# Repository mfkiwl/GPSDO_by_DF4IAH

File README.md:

# GPSDO_by_DF4IAH
GNSS or DCF77 disciplined OCXO based on hardware by DL4ZAO and DL7UKM.

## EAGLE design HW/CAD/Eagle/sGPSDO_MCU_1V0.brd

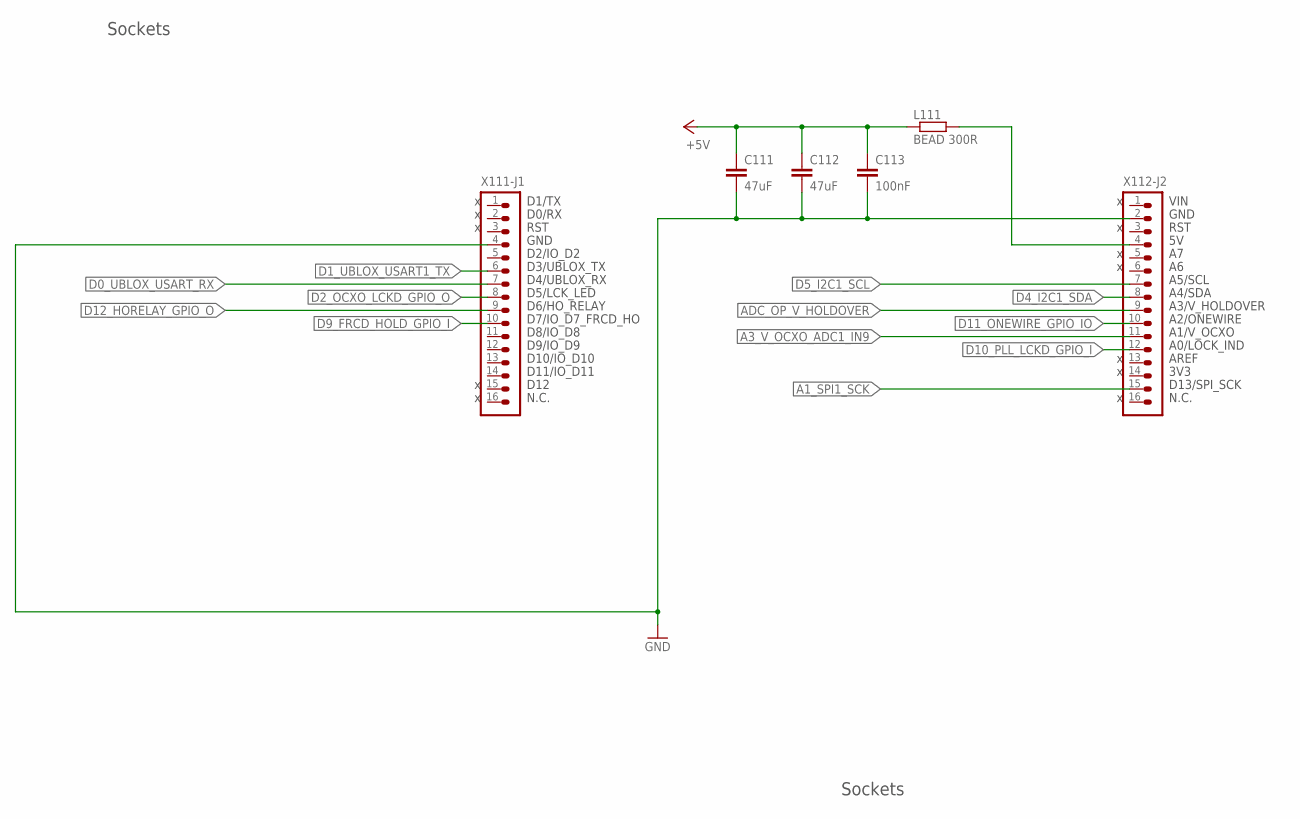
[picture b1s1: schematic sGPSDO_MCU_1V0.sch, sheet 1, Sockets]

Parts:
C111, C112: 47uF; C0805
C113: 100nF; C0805
L111: BEAD 300R; R1206
X111-J1, X112-J2: HEADER-1X16; 1X16

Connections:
+5V: C111.1, C112.1, C113.1, L111.1; also elsewhere on the board
A1_SPI1_SCK: X112-J2.15; also elsewhere on the board
A3_V_OCXO_ADC1_IN9: X112-J2.11; also elsewhere on the board
ADC_OP_V_HOLDOVER: X112-J2.9; also elsewhere on the board
D0_UBLOX_USART_RX: X111-J1.7; also elsewhere on the board
D1_UBLOX_USART1_TX: X111-J1.6; also elsewhere on the board
D2_OCXO_LCKD_GPIO_O: X111-J1.8; also elsewhere on the board
D4_I2C1_SDA: X112-J2.8; also elsewhere on the board
D5_I2C1_SCL: X112-J2.7; also elsewhere on the board
D9_FRCD_HOLD_GPIO_I: X111-J1.10; also elsewhere on the board
D10_PLL_LCKD_GPIO_I: X112-J2.12; also elsewhere on the board
D11_ONEWIRE_GPIO_IO: X112-J2.10; also elsewhere on the board
D12_HORELAY_GPIO_O: X111-J1.9; also elsewhere on the board
GND: C111.2, C112.2, C113.2, X111-J1.4, X112-J2.2; also elsewhere on the board
N112: L111.2, X112-J2.4

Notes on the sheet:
Sockets
A0/LOCK_IND
AREF
3V3
D13/SPI_SCK
N.C.
A1/V_OCXO
A2/ONEWIRE
A3/V_HOLDOVER
A4/SDA
A5/SCL
RST
GND
VIN
D12
D11/IO_D11
D10/IO_D10
D9/IO_D9
D8/IO_D8
D7/IO_D7_FRCD_HO
D6/HO_RELAY
D5/LCK_LED
D4/UBLOX_RX
D3/UBLOX_TX
D2/IO_D2
D0/RX
D1/TX

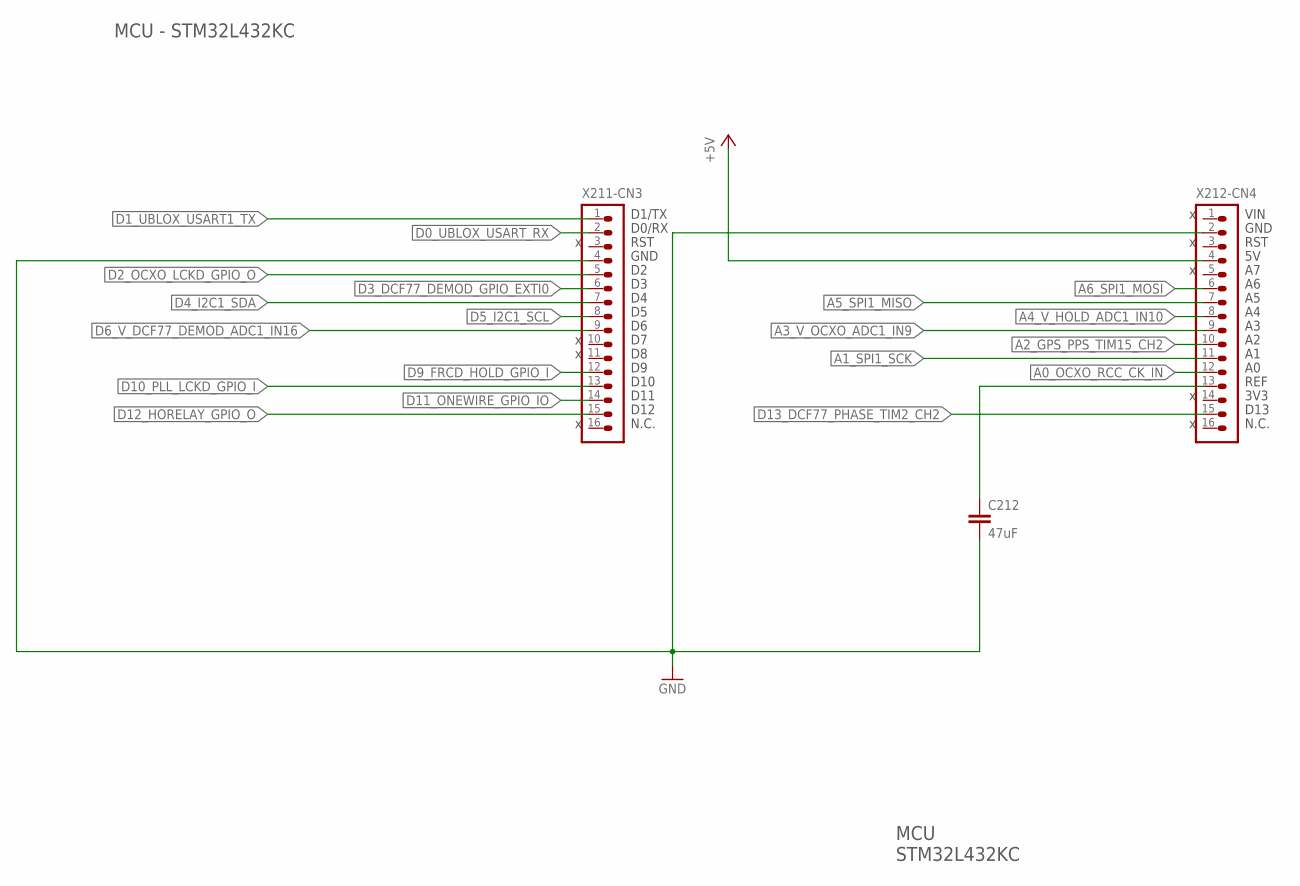
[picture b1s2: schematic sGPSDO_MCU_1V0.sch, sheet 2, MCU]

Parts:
C212: 47uF; C0805
X211-CN3, X212-CN4: HEADER-1X16; 1X16

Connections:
+5V: X212-CN4.4; also elsewhere on the board
A0_OCXO_RCC_CK_IN: X212-CN4.12; also elsewhere on the board
A1_SPI1_SCK: X212-CN4.11; also elsewhere on the board
A2_GPS_PPS_TIM15_CH2: X212-CN4.10; also elsewhere on the board
A3_V_OCXO_ADC1_IN9: X212-CN4.9; also elsewhere on the board
A4_V_HOLD_ADC1_IN10: X212-CN4.8; also elsewhere on the board
A5_SPI1_MISO: X212-CN4.7; also elsewhere on the board
A6_SPI1_MOSI: X212-CN4.6; also elsewhere on the board
D0_UBLOX_USART_RX: X211-CN3.2; also elsewhere on the board
D1_UBLOX_USART1_TX: X211-CN3.1; also elsewhere on the board
D2_OCXO_LCKD_GPIO_O: X211-CN3.5; also elsewhere on the board
D3_DCF77_DEMOD_GPIO_EXTI0: X211-CN3.6; also elsewhere on the board
D4_I2C1_SDA: X211-CN3.7; also elsewhere on the board
D5_I2C1_SCL: X211-CN3.8; also elsewhere on the board
D6_V_DCF77_DEMOD_ADC1_IN16: X211-CN3.9; also elsewhere on the board
D9_FRCD_HOLD_GPIO_I: X211-CN3.12; also elsewhere on the board
D10_PLL_LCKD_GPIO_I: X211-CN3.13; also elsewhere on the board
D11_ONEWIRE_GPIO_IO: X211-CN3.14; also elsewhere on the board
D12_HORELAY_GPIO_O: X211-CN3.15; also elsewhere on the board
D13_DCF77_PHASE_TIM2_CH2: X212-CN4.15; also elsewhere on the board
GND: C212.2, X211-CN3.4, X212-CN4.2; also elsewhere on the board
VREF: C212.1, X212-CN4.13

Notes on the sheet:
MCU - STM32L432KC
MCU STM32L432KC
REF
3V3
D13
N.C.
RST
GND
VIN
D12
D11
D10
D0/RX
D1/TX

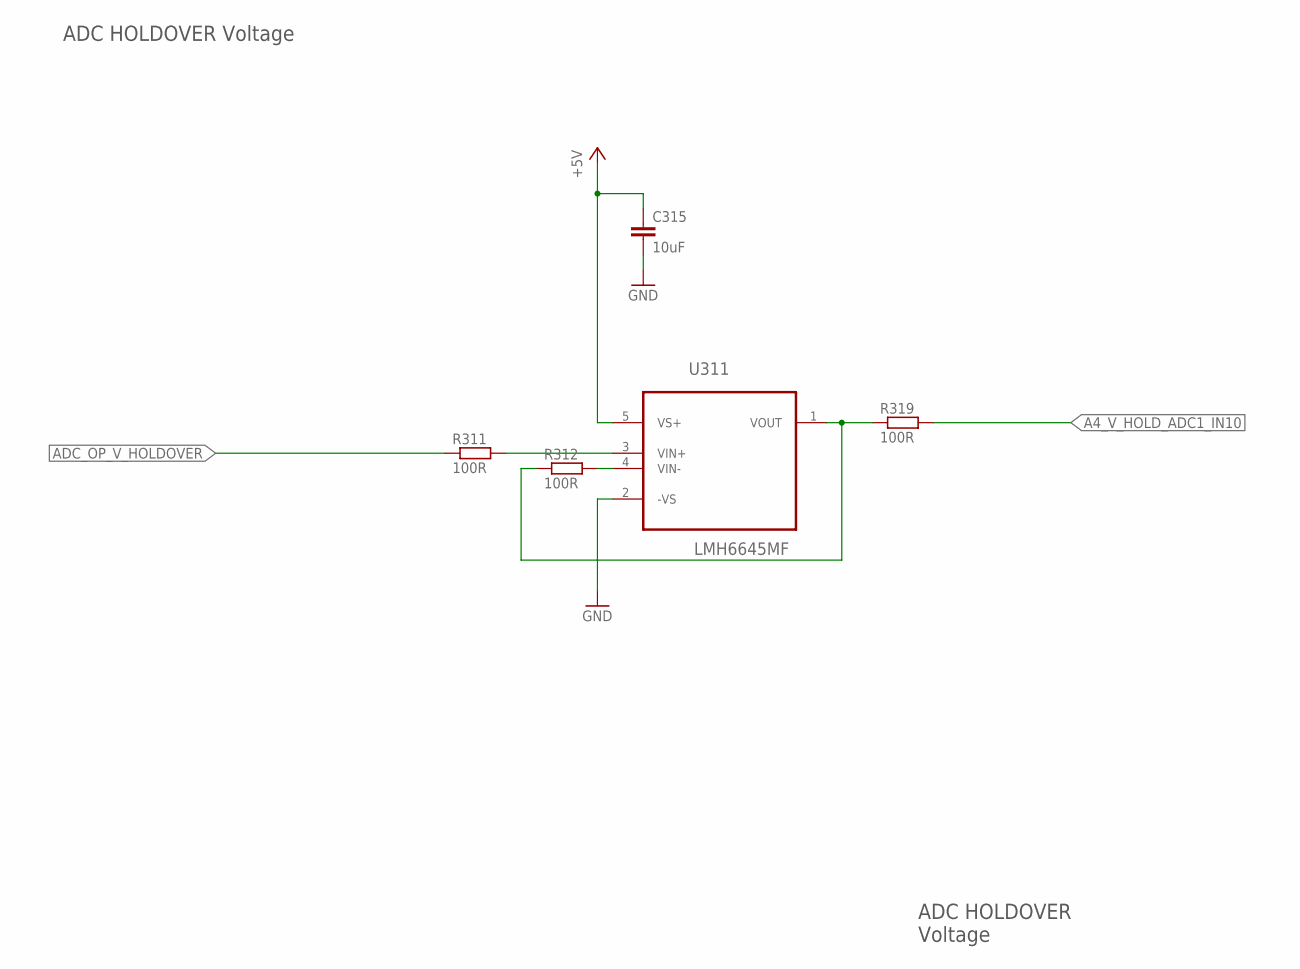
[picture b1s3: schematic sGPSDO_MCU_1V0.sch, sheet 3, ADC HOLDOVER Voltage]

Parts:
C315: 10uF; C0805
R311, R312, R319: 100R; R0805
U311: LMH6645MF; SOT-23-5

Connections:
+5V: C315.1, U311.5 (VS+); also elsewhere on the board
A4_V_HOLD_ADC1_IN10: R319.2; also elsewhere on the board
ADC_OP_V_HOLDOVER: R311.1; also elsewhere on the board
GND: C315.2, U311.2 (-VS); also elsewhere on the board
N311: R311.2, U311.3 (VIN+)
N312: R312.2, U311.4 (VIN-)
N319: R312.1, R319.1, U311.1 (VOUT)

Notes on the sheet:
ADC HOLDOVER Voltage
ADC HOLDOVER Voltage

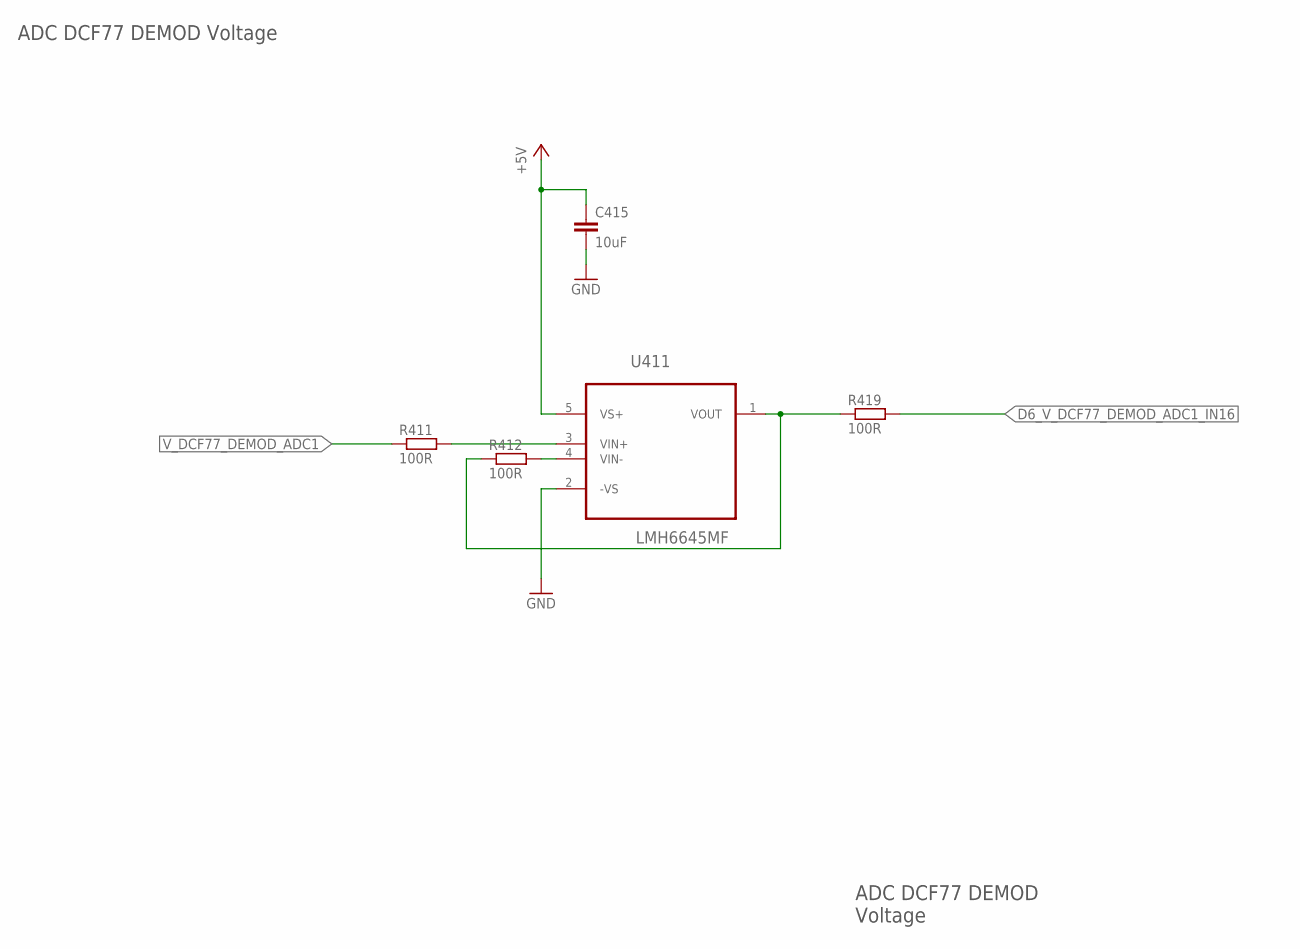
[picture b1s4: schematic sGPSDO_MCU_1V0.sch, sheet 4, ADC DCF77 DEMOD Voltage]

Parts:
C415: 10uF; C0805
R411, R412, R419: 100R; R0805
U411: LMH6645MF; SOT-23-5

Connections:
+5V: C415.1, U411.5 (VS+); also elsewhere on the board
D6_V_DCF77_DEMOD_ADC1_IN16: R419.2; also elsewhere on the board
GND: C415.2, U411.2 (-VS); also elsewhere on the board
N411: R411.2, U411.3 (VIN+)
N412: R412.2, U411.4 (VIN-)
N419: R412.1, R419.1, U411.1 (VOUT)
V_DCF77_DEMOD_ADC1: R411.1; also elsewhere on the board

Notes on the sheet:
ADC DCF77 DEMOD Voltage
ADC DCF77 DEMOD Voltage

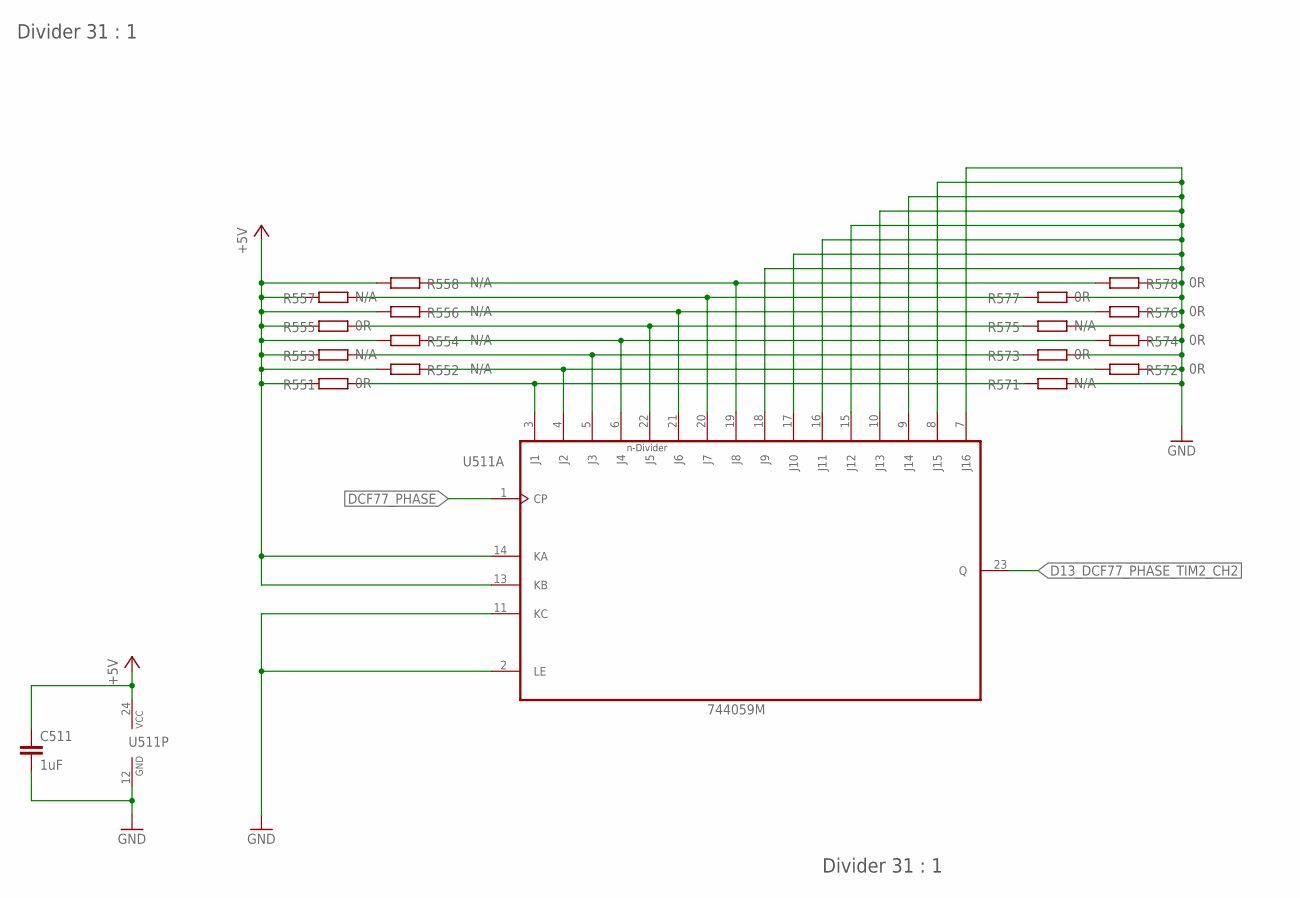
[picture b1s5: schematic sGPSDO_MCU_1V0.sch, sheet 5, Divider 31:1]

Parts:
C511: 1uF; C0805
R551, R555, R572, R573, R574, R576, R577, R578: 0R; R0402
R552, R553, R554, R556, R557, R558, R571, R575: N/A; R0402
U511: 744059M; SO24

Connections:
+5V: C511.1, R551.1, R552.1, R553.1, R554.1, R555.1, R556.1, R557.1, R558.1, U511.13 (KB), U511.14 (KA), U511.24 (VCC); also elsewhere on the board
D13_DCF77_PHASE_TIM2_CH2: U511.23 (Q); also elsewhere on the board
DCF77_PHASE: U511.1 (CP); also elsewhere on the board
GND: C511.2, R571.2, R572.2, R573.2, R574.2, R575.2, R576.2, R577.2, R578.2, U511.2 (LE), U511.7 (J16), U511.8 (J15), U511.9 (J14), U511.10 (J13), U511.11 (KC), U511.12 (GND), U511.15 (J12), U511.16 (J11), U511.17 (J10), U511.18 (J9); also elsewhere on the board
N551: R551.2, R571.1, U511.3 (J1)
N552: R552.2, R572.1, U511.4 (J2)
N553: R553.2, R573.1, U511.5 (J3)
N554: R554.2, R574.1, U511.6 (J4)
N555: R555.2, R575.1, U511.22 (J5)
N556: R556.2, R576.1, U511.21 (J6)
N557: R557.2, R577.1, U511.20 (J7)
N558: R558.2, R578.1, U511.19 (J8)

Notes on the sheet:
Divider 31 : 1

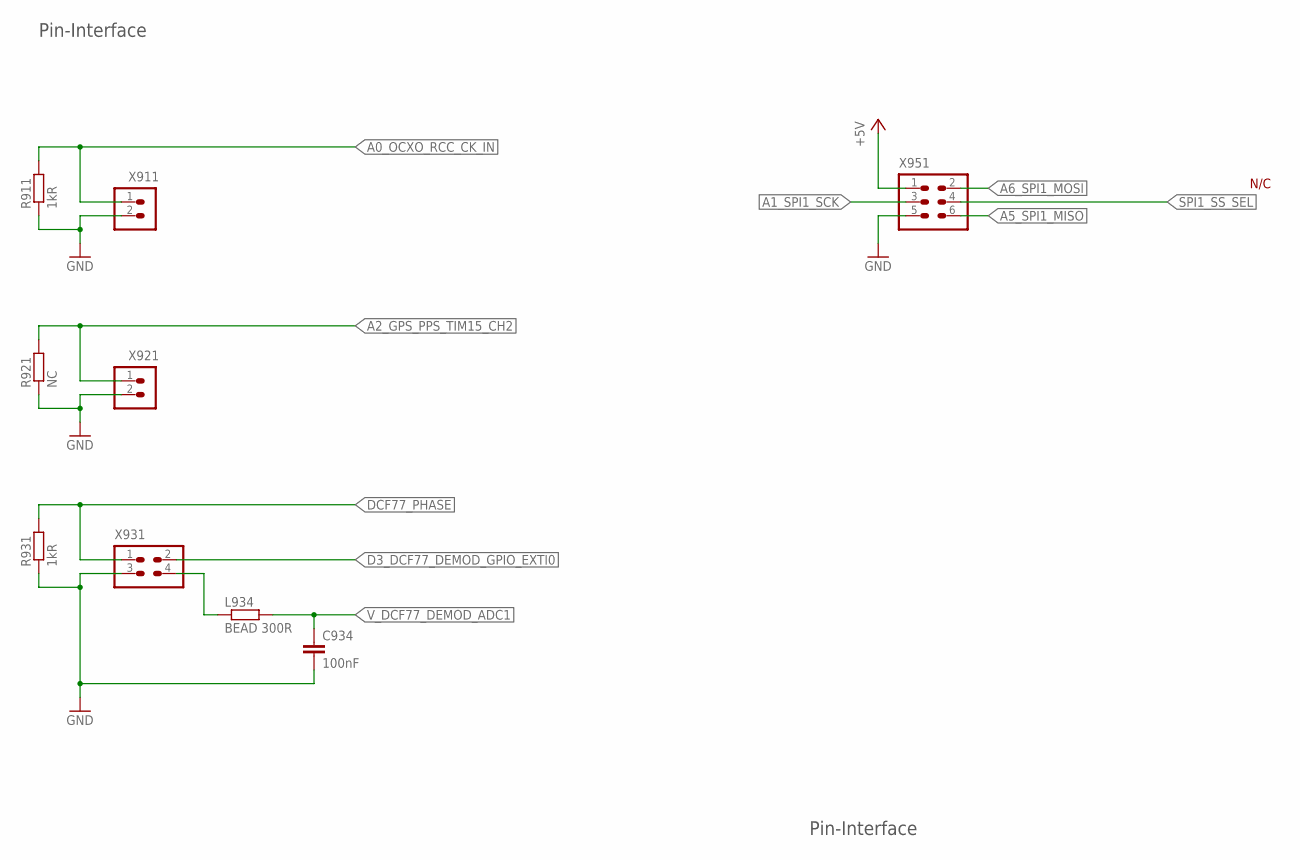
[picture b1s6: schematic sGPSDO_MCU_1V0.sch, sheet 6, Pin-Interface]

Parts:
C934: 100nF; C0805
L934: BEAD 300R; R1206
R911, R931: 1kR; R0805
R921: NC; R0805
X911, X921: HEADER-1X2; 1X02
X931: HEADER-2X2; 2X02
X951: HEADER-2X3; 2X03

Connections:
+5V: X951.1; also elsewhere on the board
A0_OCXO_RCC_CK_IN: R911.2, X911.1; also elsewhere on the board
A1_SPI1_SCK: X951.3; also elsewhere on the board
A2_GPS_PPS_TIM15_CH2: R921.2, X921.1; also elsewhere on the board
A5_SPI1_MISO: X951.6; also elsewhere on the board
A6_SPI1_MOSI: X951.2; also elsewhere on the board
D3_DCF77_DEMOD_GPIO_EXTI0: X931.2; also elsewhere on the board
DCF77_PHASE: R931.2, X931.1; also elsewhere on the board
GND: C934.2, R911.1, R921.1, R931.1, X911.2, X921.2, X931.3, X951.5; also elsewhere on the board
N934: L934.1, X931.4
SPI1_SS_SEL: X951.4
V_DCF77_DEMOD_ADC1: C934.1, L934.2; also elsewhere on the board

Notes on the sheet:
Pin-Interface
N/C

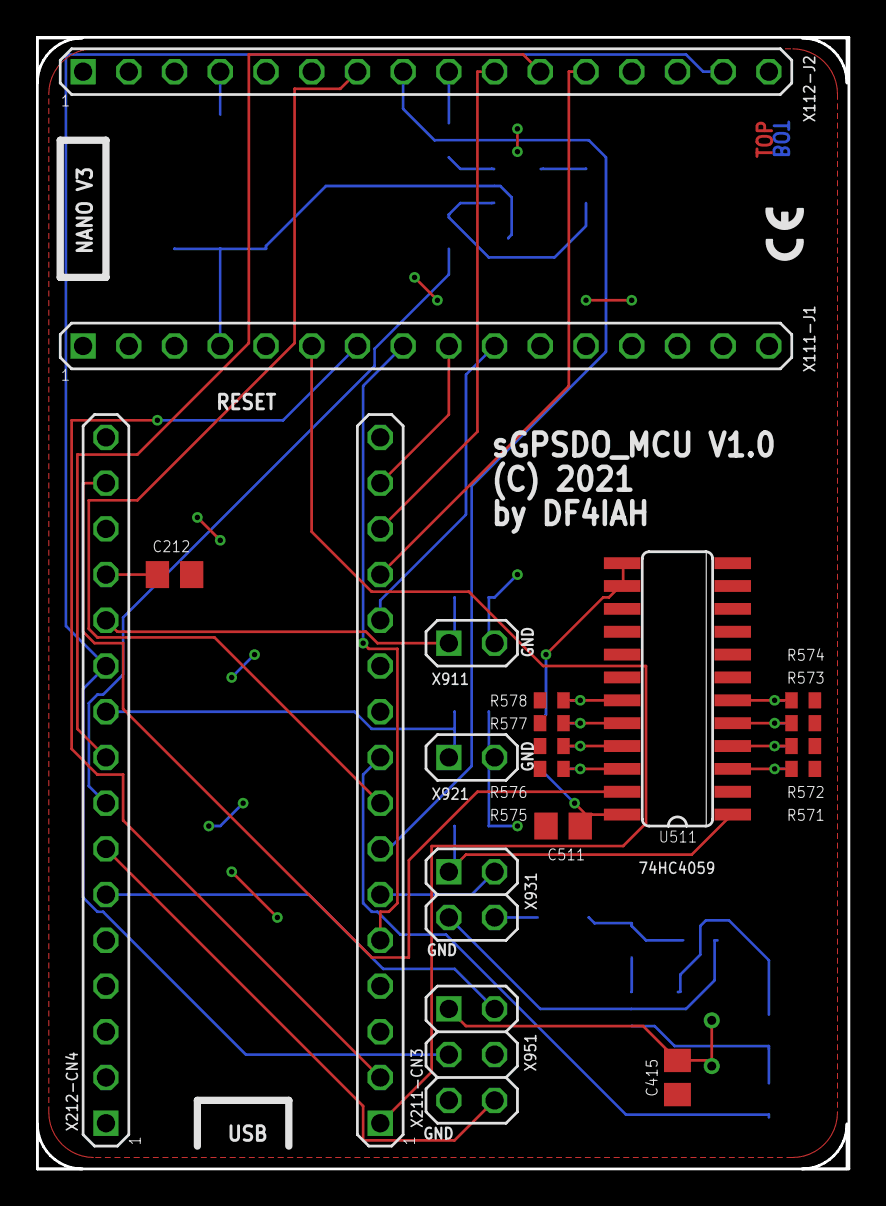
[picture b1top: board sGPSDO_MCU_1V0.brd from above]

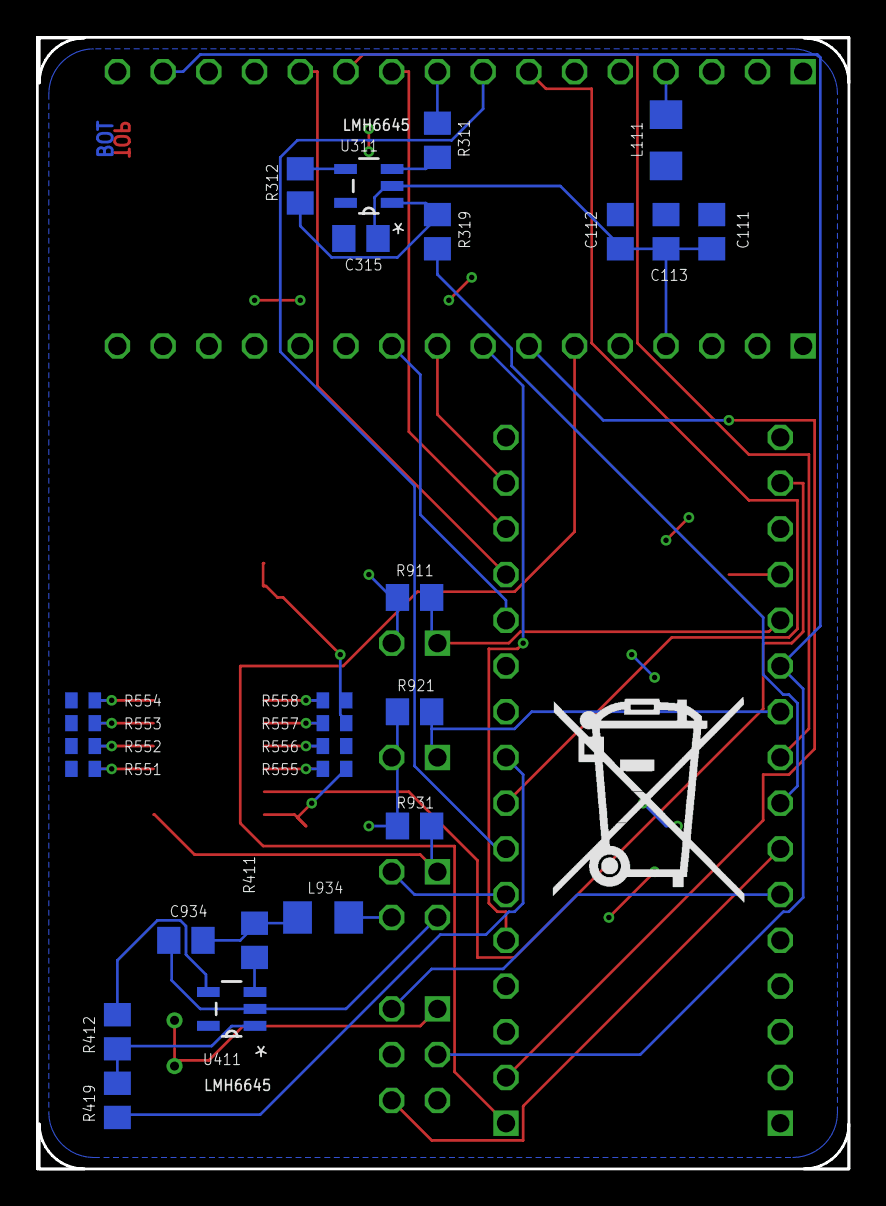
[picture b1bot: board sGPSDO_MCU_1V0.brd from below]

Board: 2 copper layers, 45.1 x 62.9 mm, 46 parts (26 on the bottom side), 41 nets.

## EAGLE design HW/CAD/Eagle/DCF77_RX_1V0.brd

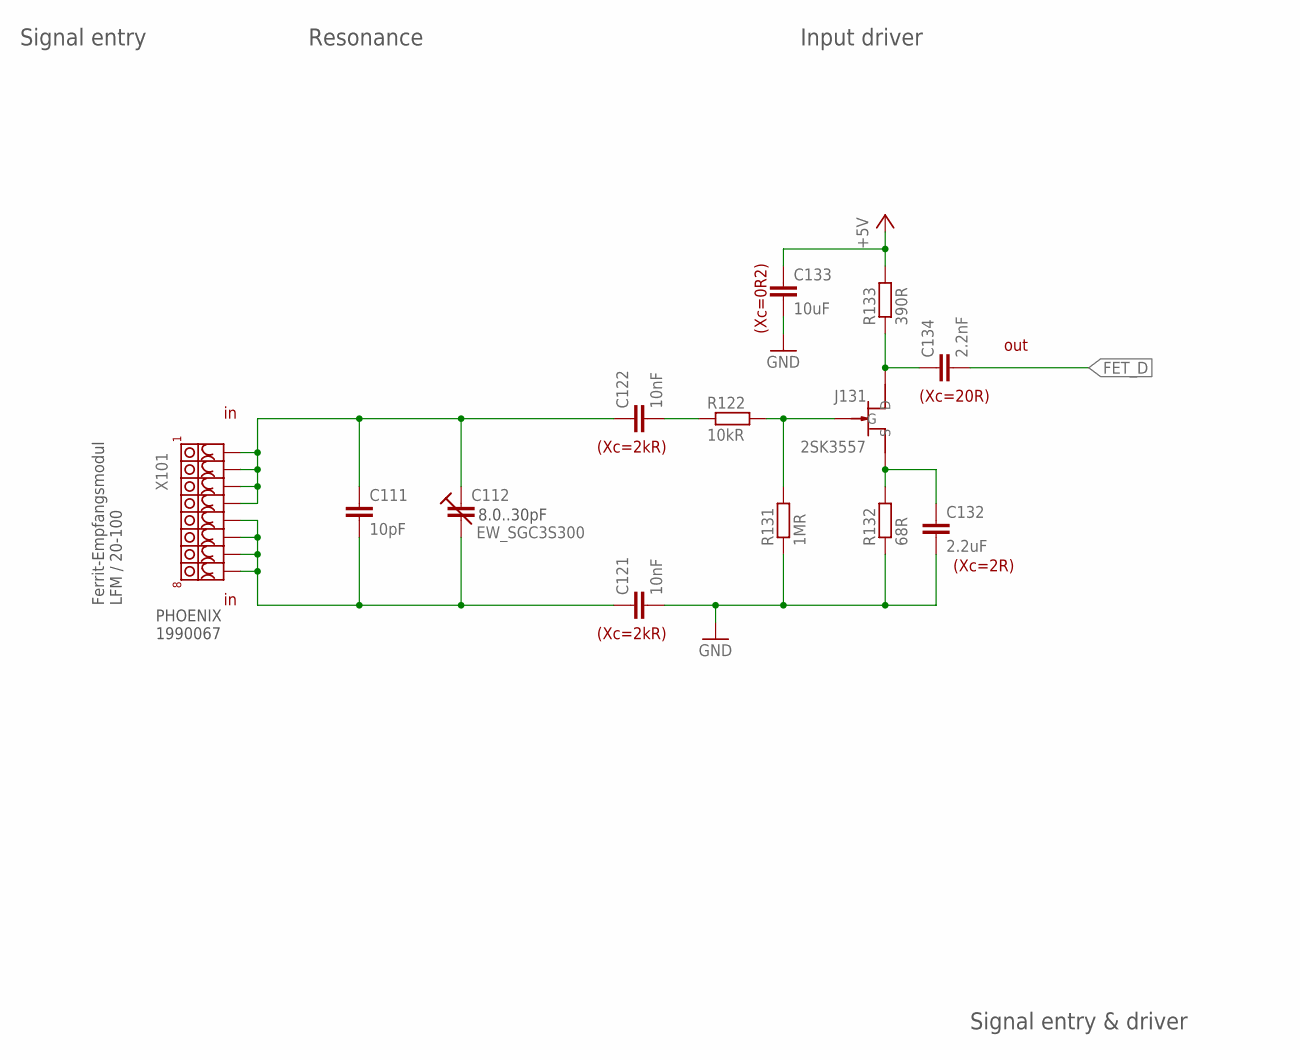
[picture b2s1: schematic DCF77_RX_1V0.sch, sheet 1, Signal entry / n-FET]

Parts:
C111: 10pF; C0402
C112: EW_SGC3S300; 4MM5_X_3MM2__EW_SGC3S
C121, C122: 10nF; C0805
C132: 2.2uF; C0805
C133: 10uF; C0805
C134: 2.2nF; C0805
J131: 2SK3557; SOT23-3
R122: 10kR; R0805
R131: 1MR; R0805
R132: 68R; R0805
R133: 390R; R0805
X101: PHOENIX_1990067_1X8X2MM50_PTSA-0-5

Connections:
+5V: C133.1, R133.2; also elsewhere on the board
FET_D: C134.2; also elsewhere on the board
GND: C121.2, C132.2, C133.2, R131.1, R132.1; also elsewhere on the board
N101: C111.2, C112.CSTAT, C121.1, X101.5, X101.6, X101.7, X101.8
N102: C111.1, C112.CROT, C122.1, X101.1, X101.2, X101.3, X101.4
N122: C122.2, R122.1
N131: J131.P$3 (G), R122.2, R131.2
N132: C132.1, J131.P$1 (S), R132.2
N133: C134.1, J131.P$2 (D), R133.1

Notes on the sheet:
Signal entry & driver
Signal entry
out
Ferrit-Empfangsmodul LFM / 20-100
8.0..30pF
PHOENIX 1990067
Input driver
Resonance
(Xc=2R)
(Xc=20R)
(Xc=0R2)
(Xc=2kR)

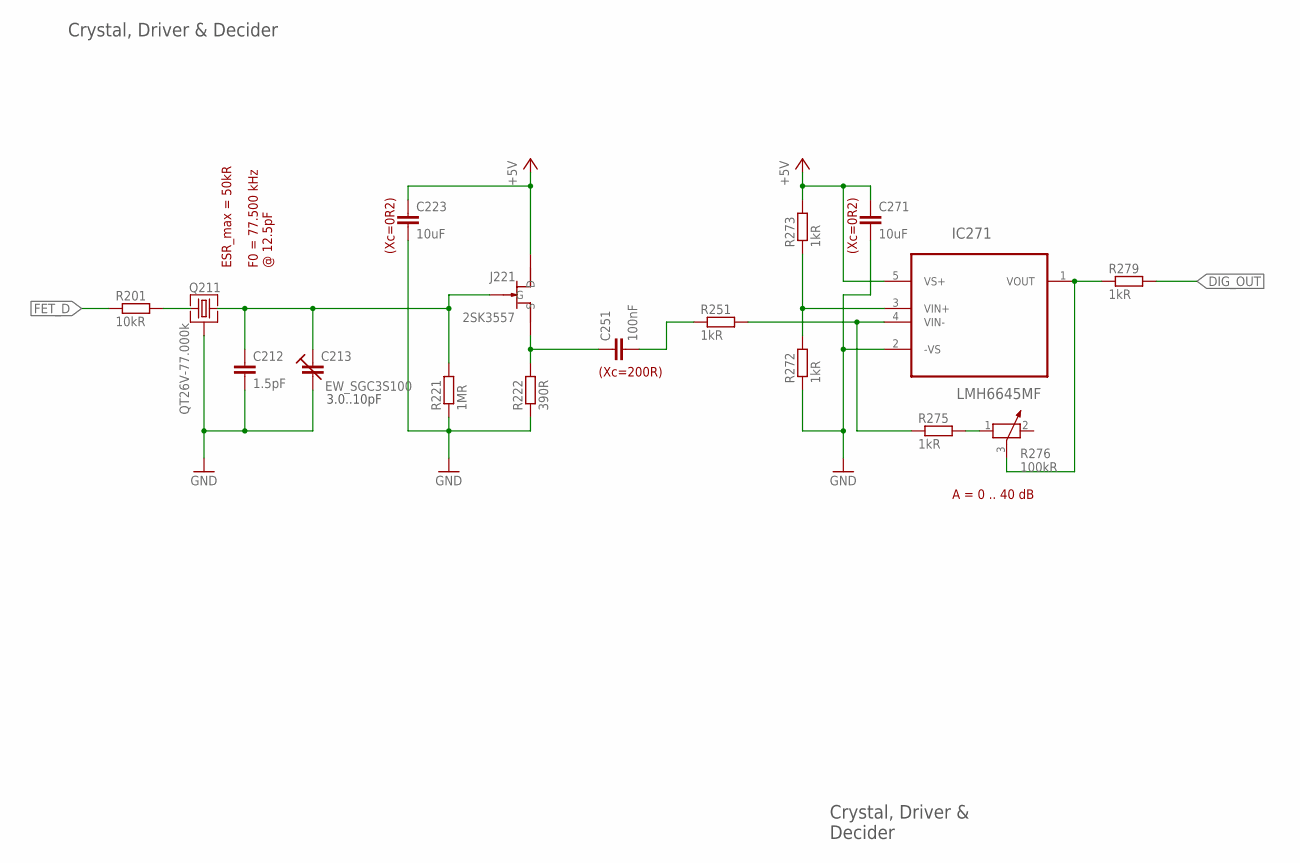
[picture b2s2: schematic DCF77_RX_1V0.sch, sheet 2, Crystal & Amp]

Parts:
C212: 1.5pF; C0402
C213: EW_SGC3S100; 4MM5_X_3MM2__EW_SGC3S
C223, C271: 10uF; C0805
C251: 100nF; C0805
IC271: LMH6645MF; SOT-23-5
J221: 2SK3557; SOT23-3
Q211: QT26V-77.000k; QT26V_QST
R201: 10kR; R0805
R221: 1MR; R0805
R222: 390R; R0805
R251, R272, R273, R275, R279: 1kR; R0805
R276: 100kR; PT-10

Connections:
+5V: C223.1, C271.1, IC271.5 (VS+), J221.P$2 (D), R273.2; also elsewhere on the board
DIG_OUT: R279.2; also elsewhere on the board
FET_D: R201.1; also elsewhere on the board
GND: C212.2, C213.CSTAT, C223.2, C271.2, IC271.2 (-VS), Q211.3, Q211.4 (3), R221.1, R222.1, R272.1; also elsewhere on the board
N221: C212.1, C213.CROT, J221.P$3 (G), Q211.2, R221.2
N222: C251.1, J221.P$1 (S), R222.2
N251: C251.2, R251.1
N271: IC271.1 (VOUT), R276.3, R279.1
N272: IC271.3 (VIN+), R272.2, R273.1
N273: IC271.4 (VIN-), R251.2, R275.1
N275: R275.2, R276.1
unnamed: Q211.1, R201.2

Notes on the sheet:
Crystal, Driver & Decider
3.0..10pF
Crystal, Driver & Decider
A = 0 .. 40 dB
ESR_max = 50kR
F0 = 77.500 kHz @ 12.5pF
(Xc=0R2)
(Xc=200R)

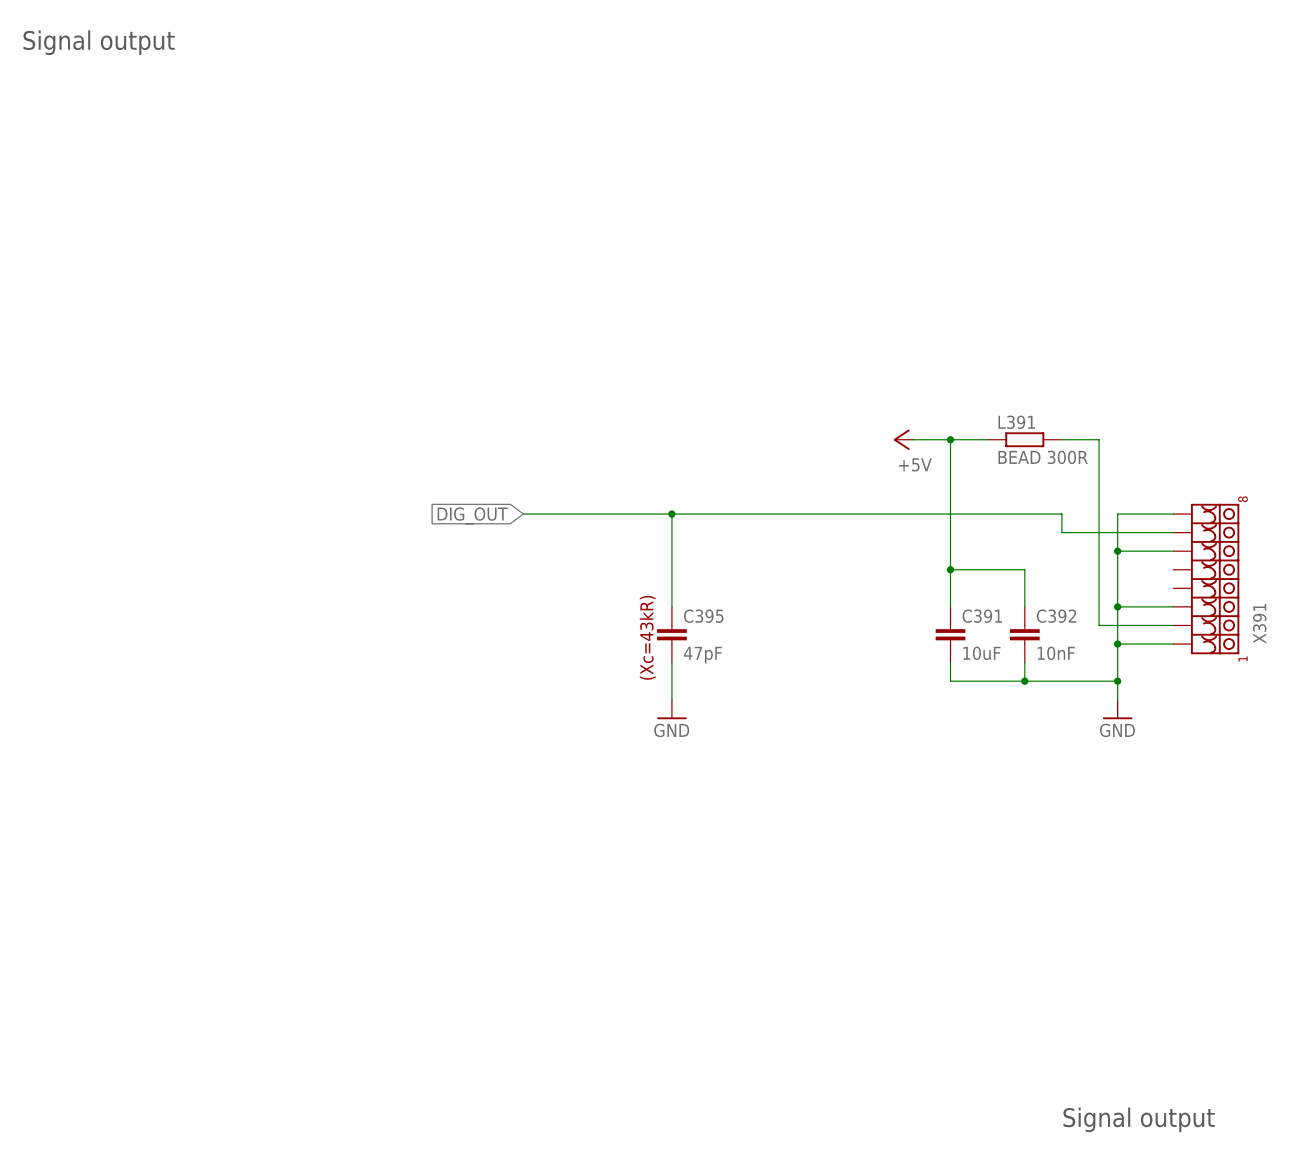
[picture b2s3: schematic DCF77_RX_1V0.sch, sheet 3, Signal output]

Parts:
C391: 10uF; C0805
C392: 10nF; C0805
C395: 47pF; C0805
L391: BEAD 300R; R1206
X391: PHOENIX_1990067_1X8X2MM50_PTSA-0-5

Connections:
+5V: C391.1, C392.1, L391.1; also elsewhere on the board
DIG_OUT: C395.1, X391.7; also elsewhere on the board
GND: C391.2, C392.2, C395.2, X391.1, X391.3, X391.6, X391.8; also elsewhere on the board
N391: L391.2, X391.2

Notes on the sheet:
Signal output
(Xc=43kR)

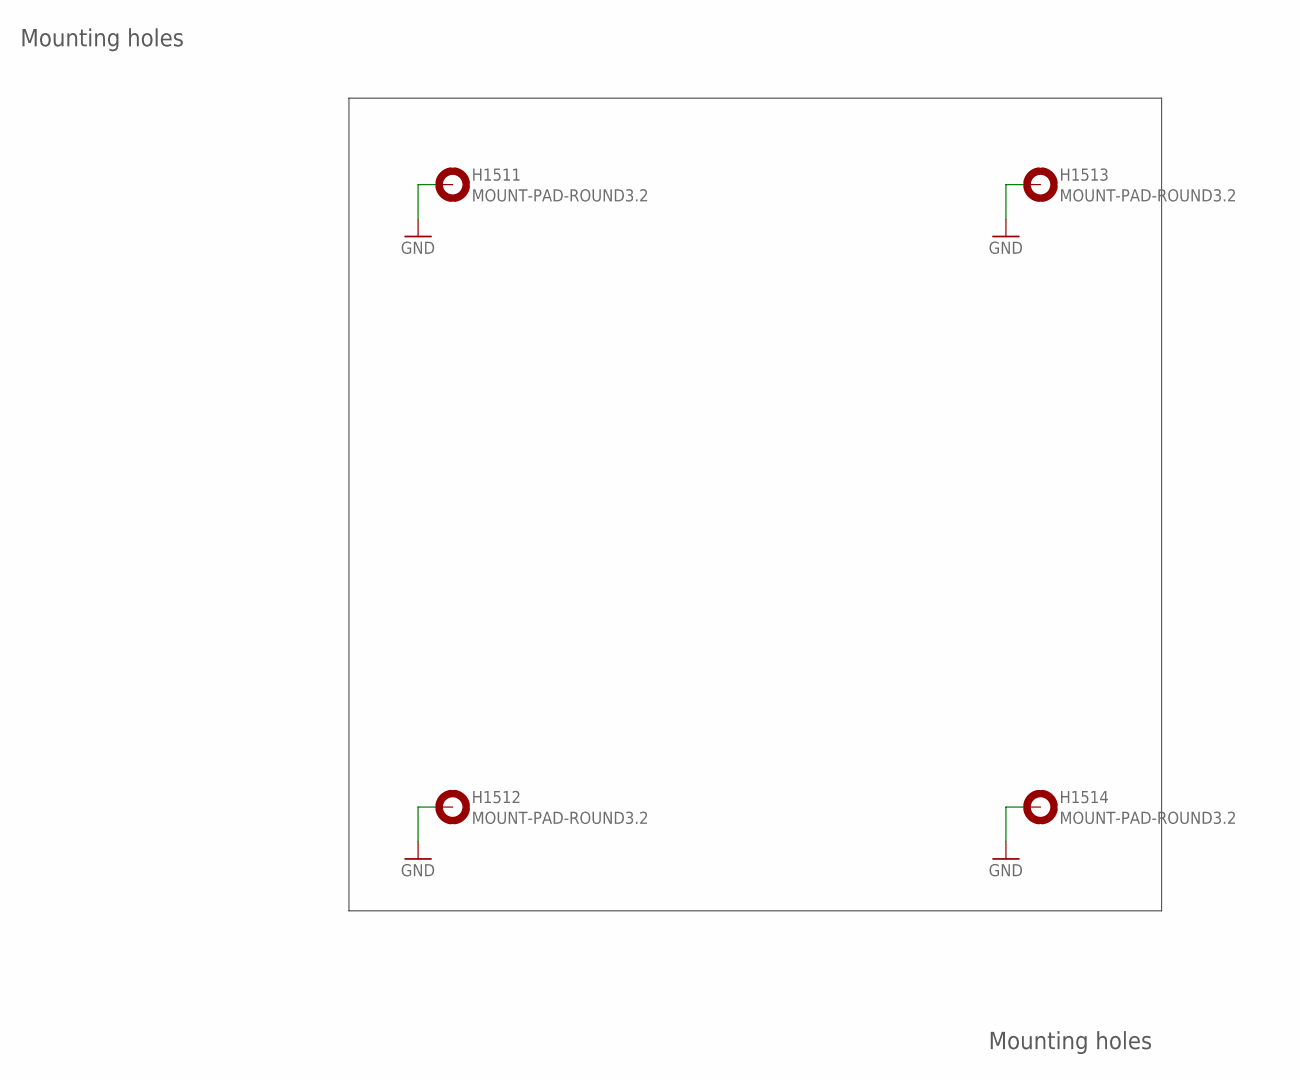
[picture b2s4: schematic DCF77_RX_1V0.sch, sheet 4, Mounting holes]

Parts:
H1511, H1512, H1513, H1514: MOUNT-PAD-ROUND3.2; 3,2-PAD

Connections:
GND: H1511.B3,2, H1512.B3,2, H1513.B3,2, H1514.B3,2; also elsewhere on the board

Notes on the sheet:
Mounting holes

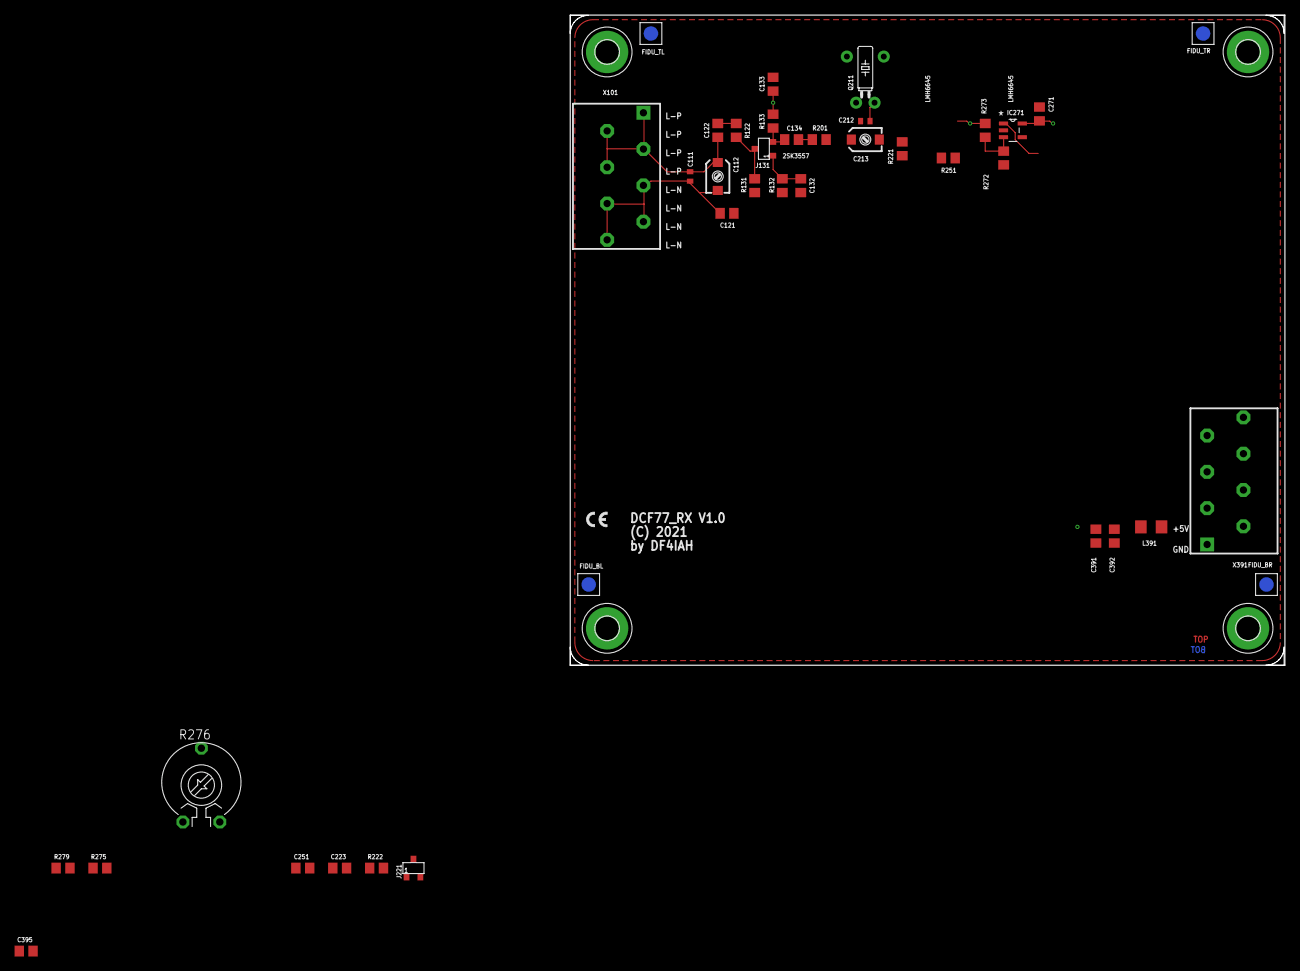
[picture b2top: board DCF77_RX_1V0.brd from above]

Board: 2 copper layers, 98.4 x 89.5 mm, 43 parts (0 on the bottom side), 19 nets.

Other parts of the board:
FIDU_BL: FIDUCIAL_MARK_1MM
FIDU_BR: FIDUCIAL_MARK_1MM
FIDU_TL: FIDUCIAL_MARK_1MM
FIDU_TR: FIDUCIAL_MARK_1MM

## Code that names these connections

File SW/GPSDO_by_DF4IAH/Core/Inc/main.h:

/* USER CODE BEGIN Header */
/**
  ******************************************************************************
  * @file           : main.h
  * @brief          : Header for main.c file.
  *                   This file contains the common defines of the application.
  ******************************************************************************
  * @attention
  *
  * <h2><center>&copy; Copyright (c) 2021 STMicroelectronics.
  * All rights reserved.</center></h2>
  *
  * This software component is licensed by ST under BSD 3-Clause license,
  * the "License"; You may not use this file except in compliance with the
  * License. You may obtain a copy of the License at:
  *                        opensource.org/licenses/BSD-3-Clause
  *
  ******************************************************************************
  */
/* USER CODE END Header */

/* Define to prevent recursive inclusion -------------------------------------*/
#ifndef __MAIN_H
#define __MAIN_H

#ifdef __cplusplus
extern "C" {
#endif

/* Includes ------------------------------------------------------------------*/
#include "stm32l4xx_hal.h"

/* Private includes ----------------------------------------------------------*/
/* USER CODE BEGIN Includes */

/* USER CODE END Includes */

/* Exported types ------------------------------------------------------------*/
/* USER CODE BEGIN ET */

/* USER CODE END ET */

/* Exported constants --------------------------------------------------------*/
/* USER CODE BEGIN EC */

/* USER CODE END EC */

/* Exported macro ------------------------------------------------------------*/
/* USER CODE BEGIN EM */

/* USER CODE END EM */

/* Exported functions prototypes ---------------------------------------------*/
void Error_Handler(void);

/* USER CODE BEGIN EFP */

/* USER CODE END EFP */

/* Private defines -----------------------------------------------------------*/
#define NoD7_RCC_OSC32_IN_Pin GPIO_PIN_14
#define NoD7_RCC_OSC32_IN_GPIO_Port GPIOC
#define NoD8_RCC_OSC32_OUT_Pin GPIO_PIN_15
#define NoD8_RCC_OSC32_OUT_GPIO_Port GPIOC
#define A0_OCXO_RCC_CK_IN_Pin GPIO_PIN_0
#define A0_OCXO_RCC_CK_IN_GPIO_Port GPIOA
#define A1_SPI1_SCK_Pin GPIO_PIN_1
#define A1_SPI1_SCK_GPIO_Port GPIOA
#define NoA7_TERMINAL_USART2_TX_Pin GPIO_PIN_2
#define NoA7_TERMINAL_USART2_TX_GPIO_Port GPIOA
#define A2_GPS_PPS_TIM15_CH2_Pin GPIO_PIN_3
#define A2_GPS_PPS_TIM15_CH2_GPIO_Port GPIOA
#define A3_V_OCXO_ADC1_IN9_Pin GPIO_PIN_4
#define A3_V_OCXO_ADC1_IN9_GPIO_Port GPIOA
#define A4_V_HOLD_ADC1_IN10_Pin GPIO_PIN_5
#define A4_V_HOLD_ADC1_IN10_GPIO_Port GPIOA
#define A5_SPI1_MISO_Pin GPIO_PIN_6
#define A5_SPI1_MISO_GPIO_Port GPIOA
#define A6_SPI1_MOSI_Pin GPIO_PIN_7
#define A6_SPI1_MOSI_GPIO_Port GPIOA
#define D3_DCF77_DEMOD_GPIO_EXTI0_Pin GPIO_PIN_0
#define D3_DCF77_DEMOD_GPIO_EXTI0_GPIO_Port GPIOB
#define D6_V_DCF77_DEMOD_ADC1_IN16_Pin GPIO_PIN_1
#define D6_V_DCF77_DEMOD_ADC1_IN16_GPIO_Port GPIOB
#define D9_FRCD_HOLD_GPIO_I_Pin GPIO_PIN_8
#define D9_FRCD_HOLD_GPIO_I_GPIO_Port GPIOA
#define D1_UBLOX_USART1_TX_Pin GPIO_PIN_9
#define D1_UBLOX_USART1_TX_GPIO_Port GPIOA
#define D0_UBLOX_USART1_RX_Pin GPIO_PIN_10
#define D0_UBLOX_USART1_RX_GPIO_Port GPIOA
#define D10_PLL_LCKD_GPIO_I_Pin GPIO_PIN_11
#define D10_PLL_LCKD_GPIO_I_GPIO_Port GPIOA
#define D2_OCXO_LCKD_GPIO_O_Pin GPIO_PIN_12
#define D2_OCXO_LCKD_GPIO_O_GPIO_Port GPIOA
#define NoJ1J2_SYS_JTMS_SWDIO_Pin GPIO_PIN_13
#define NoJ1J2_SYS_JTMS_SWDIO_GPIO_Port GPIOA
#define NoJ1J2_SYS_JTCK_SWCLK_Pin GPIO_PIN_14
#define NoJ1J2_SYS_JTCK_SWCLK_GPIO_Port GPIOA
#define NoJ1J2_TERMINAL_USART2_RX_Pin GPIO_PIN_15
#define NoJ1J2_TERMINAL_USART2_RX_GPIO_Port GPIOA
#define D13_DCF77_PHASE_TIM2_CH2_Pin GPIO_PIN_3
#define D13_DCF77_PHASE_TIM2_CH2_GPIO_Port GPIOB
#define D12_HoRelay_GPIO_O_Pin GPIO_PIN_4
#define D12_HoRelay_GPIO_O_GPIO_Port GPIOB
#define D11_ONEWIRE_GPIO_IO_Pin GPIO_PIN_5
#define D11_ONEWIRE_GPIO_IO_GPIO_Port GPIOB
#define D5_I2C1_SCL_Pin GPIO_PIN_6
#define D5_I2C1_SCL_GPIO_Port GPIOB
#define D4_I2C1_SDA_Pin GPIO_PIN_7
#define D4_I2C1_SDA_GPIO_Port GPIOB
#define NoJ1J2_BOOT0_GPIO_I_Pin GPIO_PIN_3
#define NoJ1J2_BOOT0_GPIO_I_GPIO_Port GPIOH
/* USER CODE BEGIN Private defines */

/* Turn off logging when not needed */
//#define LOGGING

/* Default: VCXO is displined by hardware PLL */
#define PLL_BY_SOFTWARE
#define DCF77_ENABLED

/* Onewire settings */
#define ONEWIRE_DEVICES_MAX								2

#define ONEWIRE_DS18B20_ADC_12B
//#define ONEWIRE_DS18B20_ADC_11B
//#define ONEWIRE_DS18B20_ADC_10B
//#define ONEWIRE_DS18B20_ADC_09B

#define ONEWIRE_DS18B20_ALARM_LO						40
#define ONEWIRE_DS18B20_ALARM_HI						50

/* ublox NEO settings */
#define UBLOX_MAX_CH									24

/* Software-PLL tuning parameters */
#define SW_PLL_TUNE_FAST								 50000.0f
#define SW_PLL_TUNE_SLOW								200000.0f


/* USER CODE END Private defines */

#ifdef __cplusplus
}
#endif

#endif /* __MAIN_H */
